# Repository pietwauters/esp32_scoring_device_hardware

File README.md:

# esp32_scoring_device_hardware
Hardware files for the [low cost scoring device based on a esp32 development board](https://github.com/pietwauters/esp32-scoring-device/wiki). The Wiki is slightly outdated as we now use an update for the PCB. It is just there for historical reasons. There is a [walkthrough on how to assemble the scoring device](https://github.com/pietwauters/esp32_scoring_device_hardware/blob/main/Walkthrough%20to%20buildOpenPiste%20%20Fencing%20Scoring%20Machine.docx).
The current firmware is found on [latest version of the firmware](https://github.com/pietwauters/esp32scoringdeviceMqtt)

You can use the same hardware to make an accurate [wire / weapon tester](https://github.com/pietwauters/WeaponWireTester). (You only have to replace the 470 Ohm resitors by 47 Ohm resistor) See: https://github.com/pietwauters/WeaponWireTester

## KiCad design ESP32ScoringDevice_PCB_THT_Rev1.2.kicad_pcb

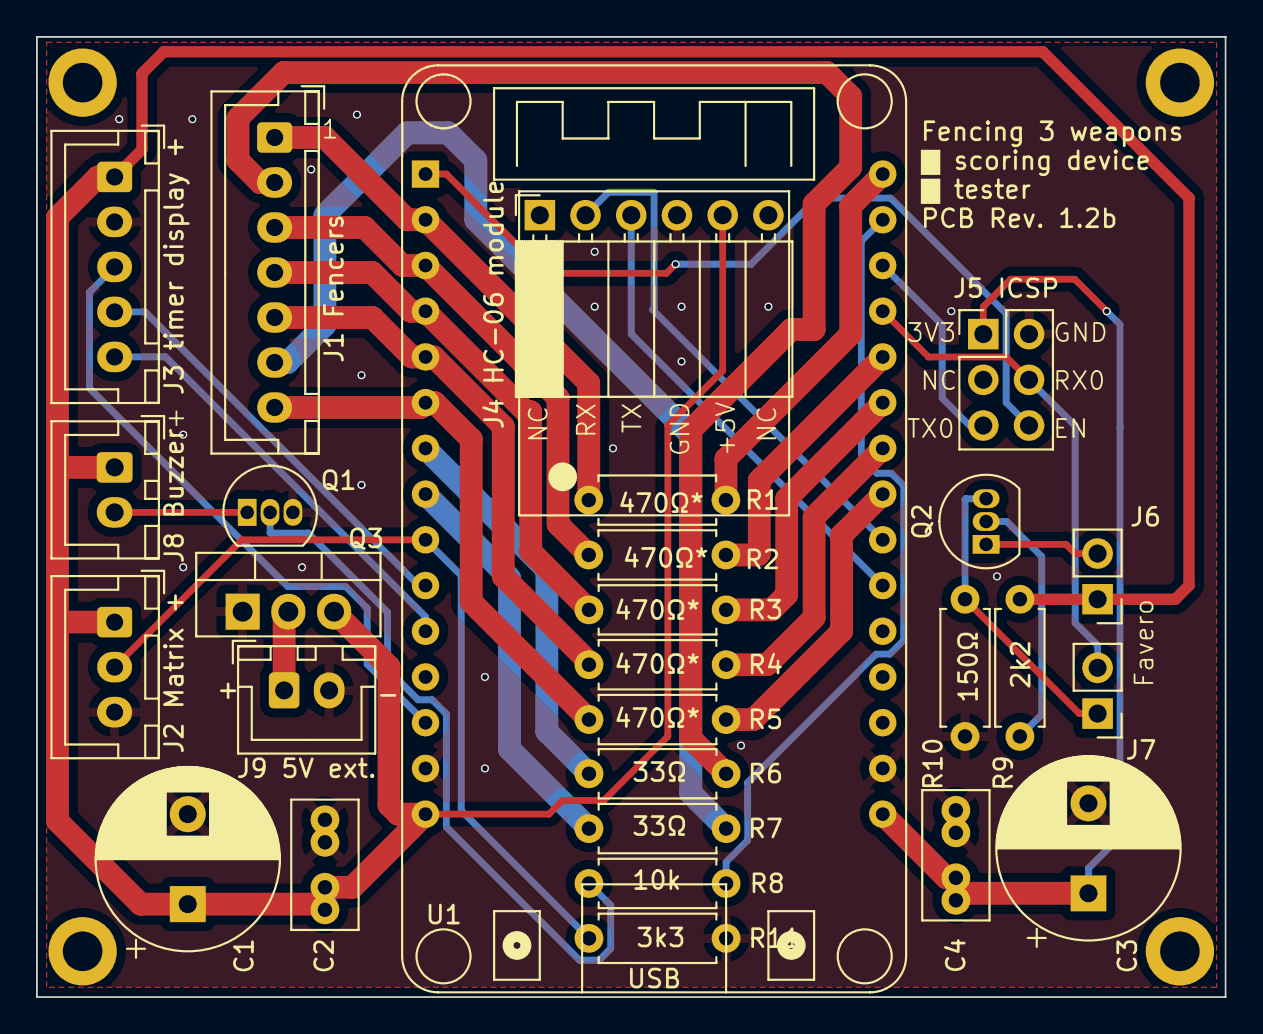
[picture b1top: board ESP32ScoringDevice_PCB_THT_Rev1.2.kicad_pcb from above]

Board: 2 copper layers, 66.0 x 53.3 mm, 32 parts (0 on the bottom side), 33 nets.

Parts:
C1, C3: 470µF; CP_Radial_D10.0mm_P5.00mm
C2, C4: 100nF; C_Rect_L7.0mm_W3.5mm_P2.50mm_P5.00mm
H1, H2, H3, H4: MountingHole_2.2mm_M2_DIN965_Pad
J1 Fencers: Fencers; JST_XH_B7B-XH-A_1x07_P2.50mm_Vertical
J2 Matrix +: WS2812B LED Matrix; JST_XH_B3B-XH-A_1x03_P2.50mm_Vertical
J3 timer display +: MAX7219 Timer Display; JST_XH_B5B-XH-A_1x05_P2.50mm_Vertical
J4 HC-06 module: HC-06 BT module; PinSocket_1x06_P2.54mm_Horizontal
J5 ICSP: ICSP; PinHeader_2x03_P2.54mm_Vertical
J6, J7: Conn_01x02; PinHeader_1x02_P2.54mm_Vertical
J8 Buzzer: Buzzer; JST_XH_B2B-XH-A_1x02_P2.50mm_Vertical
J9 5V ext.: 5V ext. Power; JST_XH_B2B-XH-A_1x02_P2.50mm_Vertical
Q1, Q2: BC337; TO-92_Inline
Q3: FQP27P06; TO-220-3_Vertical
R1, R2, R3, R4, R5: 470Ω; R_Axial_DIN0207_L6.3mm_D2.5mm_P7.62mm_Horizontal
R6, R7: 33Ω; R_Axial_DIN0207_L6.3mm_D2.5mm_P7.62mm_Horizontal
R8: 3k3; R_Axial_DIN0207_L6.3mm_D2.5mm_P7.62mm_Horizontal
R9: 2k2; R_Axial_DIN0207_L6.3mm_D2.5mm_P7.62mm_Horizontal
R10: 150Ω; R_Axial_DIN0207_L6.3mm_D2.5mm_P7.62mm_Horizontal
R11: 10k; R_Axial_DIN0207_L6.3mm_D2.5mm_P7.62mm_Horizontal
U1: ESP32_DevKit_V1_DOIT 30pin; esp32_devkit_v1_doit

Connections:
+3.3V: C3.1, C4.1, J5 ICSP.1, U1.16 (3V3)
+5V: C1.1, C2.1, J2 Matrix +.1, J3 timer display +.1, J4 HC-06 module.5, J6.1, J8 Buzzer.1, Q3.3 (S), R9.2, U1.15 (VIN)
GND: C1.2, C2.2, C3.2, C4.2, J2 Matrix +.3, J3 timer display +.2, J4 HC-06 module.4, J5 ICSP.2, J9 5V ext..2, Q1.3 (E), Q3.1 (G), R10.2, R11.2, U1.14 (GND), U1.17 (GND)
unnamed: J1 Fencers.1, R1.2, U1.2 (SENSOR_VP)
unnamed: J1 Fencers.2, R6.2
unnamed: J1 Fencers.3, R2.1, U1.3 (SENSOR_VN)
unnamed: J1 Fencers.4, R3.2, U1.4 (IO34)
unnamed: J1 Fencers.5, R4.2, U1.5 (IO35)
unnamed: J1 Fencers.6, R7.2
unnamed: J1 Fencers.7, R5.2, U1.6 (IO32)
unnamed: J2 Matrix +.2, R11.1, U1.9 (IO26)
unnamed: J3 timer display +.3, U1.13 (IO13)
unnamed: J3 timer display +.4, U1.10 (IO27)
unnamed: J3 timer display +.5, U1.11 (IO14)
unnamed: J4 HC-06 module.2, U1.22 (IO17)
unnamed: J4 HC-06 module.3, U1.21 (IO16)
unnamed: J5 ICSP.4, J7.2, U1.27 (RXD0/IO3)
unnamed: J5 ICSP.5, U1.28 (TXD0/IO1)
unnamed: J5 ICSP.6, U1.1 (EN)
unnamed: J6.2, Q2.1 (C)
unnamed: J7.1, Q2.3 (E), R10.1
unnamed: J8 Buzzer.2, Q1.1 (C)
unnamed: J9 5V ext..1, Q3.2 (D)
unnamed: Q1.2 (B), R8.1
unnamed: Q2.2 (B), R9.1
unnamed: R5.1, U1.23 (IO5)
unnamed: R4.1, U1.24 (IO18)
unnamed: R3.1, U1.25 (IO19)
unnamed: R2.2, U1.26 (IO21)
unnamed: R8.2, U1.29 (IO22)
unnamed: R1.1, U1.30 (IO23)
unnamed: R7.1, U1.8 (IO25)
unnamed: R6.1, U1.7 (IO33)

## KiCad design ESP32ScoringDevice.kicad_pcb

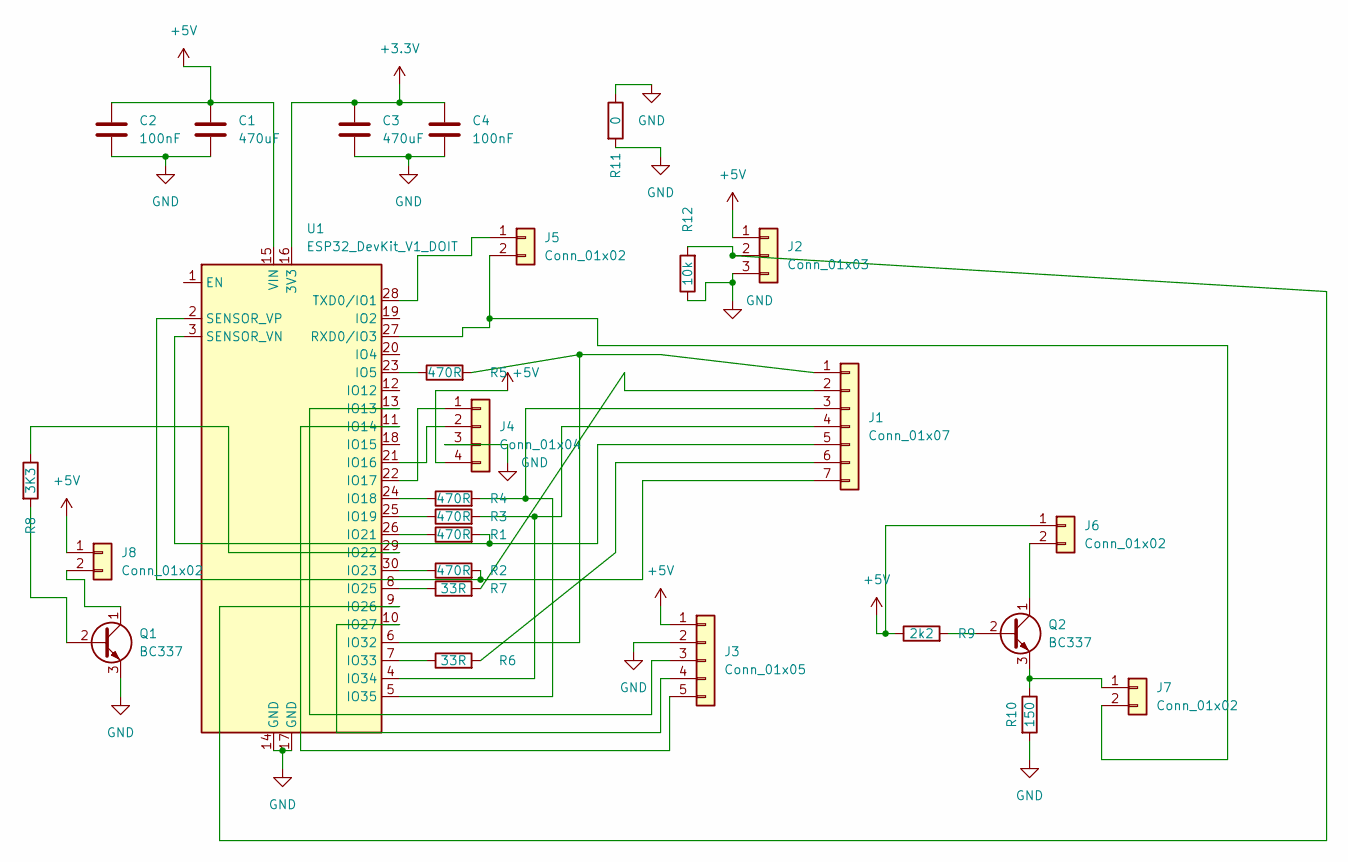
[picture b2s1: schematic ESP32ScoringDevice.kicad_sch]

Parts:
C1, C3: 470uF; CP_Radial_D10.0mm_P5.00mm
C2, C4: 100nF; C_Rect_L7.2mm_W2.5mm_P5.00mm_FKS2_FKP2_MKS2_MKP2
J1: Conn_01x07; PinHeader_1x07_P2.54mm_Vertical
J2: Conn_01x03; PinHeader_1x03_P2.54mm_Vertical
J3: Conn_01x05; PinHeader_1x05_P2.54mm_Vertical
J4: Conn_01x04; PinHeader_1x04_P2.54mm_Vertical
J5, J6, J7, J8: Conn_01x02; PinHeader_1x02_P2.54mm_Vertical
Q1, Q2: BC337; TO-92_Inline
R1, R2, R3, R4, R5: 470R; R_Axial_DIN0207_L6.3mm_D2.5mm_P10.16mm_Horizontal
R6, R7: 33R; R_Axial_DIN0207_L6.3mm_D2.5mm_P10.16mm_Horizontal
R8: 3K3; R_Axial_DIN0207_L6.3mm_D2.5mm_P10.16mm_Horizontal
R9: 2k2; R_Axial_DIN0207_L6.3mm_D2.5mm_P10.16mm_Horizontal
R10: 150; R_Axial_DIN0207_L6.3mm_D2.5mm_P10.16mm_Horizontal
R11: 0; R_Axial_DIN0207_L6.3mm_D2.5mm_P15.24mm_Horizontal
R12: 10k; R_Axial_DIN0207_L6.3mm_D2.5mm_P10.16mm_Horizontal
U1: ESP32_DevKit_V1_DOIT; esp32_devkit_v1_doit

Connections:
+3.3V: C3.1, C4.1, U1.16 (3V3)
+5V: C1.1, C2.1, J2.1, J3.1, J4.4, J6.1, J8.1, R9.1, U1.15 (VIN)
GND: C1.2, C2.2, C3.2, C4.2, J2.3, J3.2, J4.3, Q1.3 (E), R10.2, R11.1, R11.2, R12.1, U1.14 (GND), U1.17 (GND)
unnamed: J1.1, R5.2, U1.6 (IO32)
unnamed: J1.2, R7.2
unnamed: J1.3, R4.2, U1.5 (IO35)
unnamed: J1.4, R3.2, U1.4 (IO34)
unnamed: J1.5, R1.2, U1.3 (SENSOR_VN)
unnamed: J1.6, R6.2
unnamed: J1.7, R2.2, U1.2 (SENSOR_VP)
unnamed: J2.2, R12.2, U1.9 (IO26)
unnamed: J3.3, U1.13 (IO13)
unnamed: J3.4, U1.10 (IO27)
unnamed: J3.5, U1.11 (IO14)
unnamed: J4.1, U1.22 (IO17)
unnamed: J4.2, U1.21 (IO16)
unnamed: J5.1, U1.28 (TXD0/IO1)
unnamed: J5.2, J7.2, U1.27 (RXD0/IO3)
unnamed: J6.2, Q2.1 (C)
unnamed: J7.1, Q2.3 (E), R10.1
unnamed: J8.2, Q1.1 (C)
unnamed: Q1.2 (B), R8.2
unnamed: Q2.2 (B), R9.2
unnamed: R1.1, U1.26 (IO21)
unnamed: R2.1, U1.30 (IO23)
unnamed: R3.1, U1.25 (IO19)
unnamed: R4.1, U1.24 (IO18)
unnamed: R5.1, U1.23 (IO5)
unnamed: R6.1, U1.7 (IO33)
unnamed: R7.1, U1.8 (IO25)
unnamed: R8.1, U1.29 (IO22)

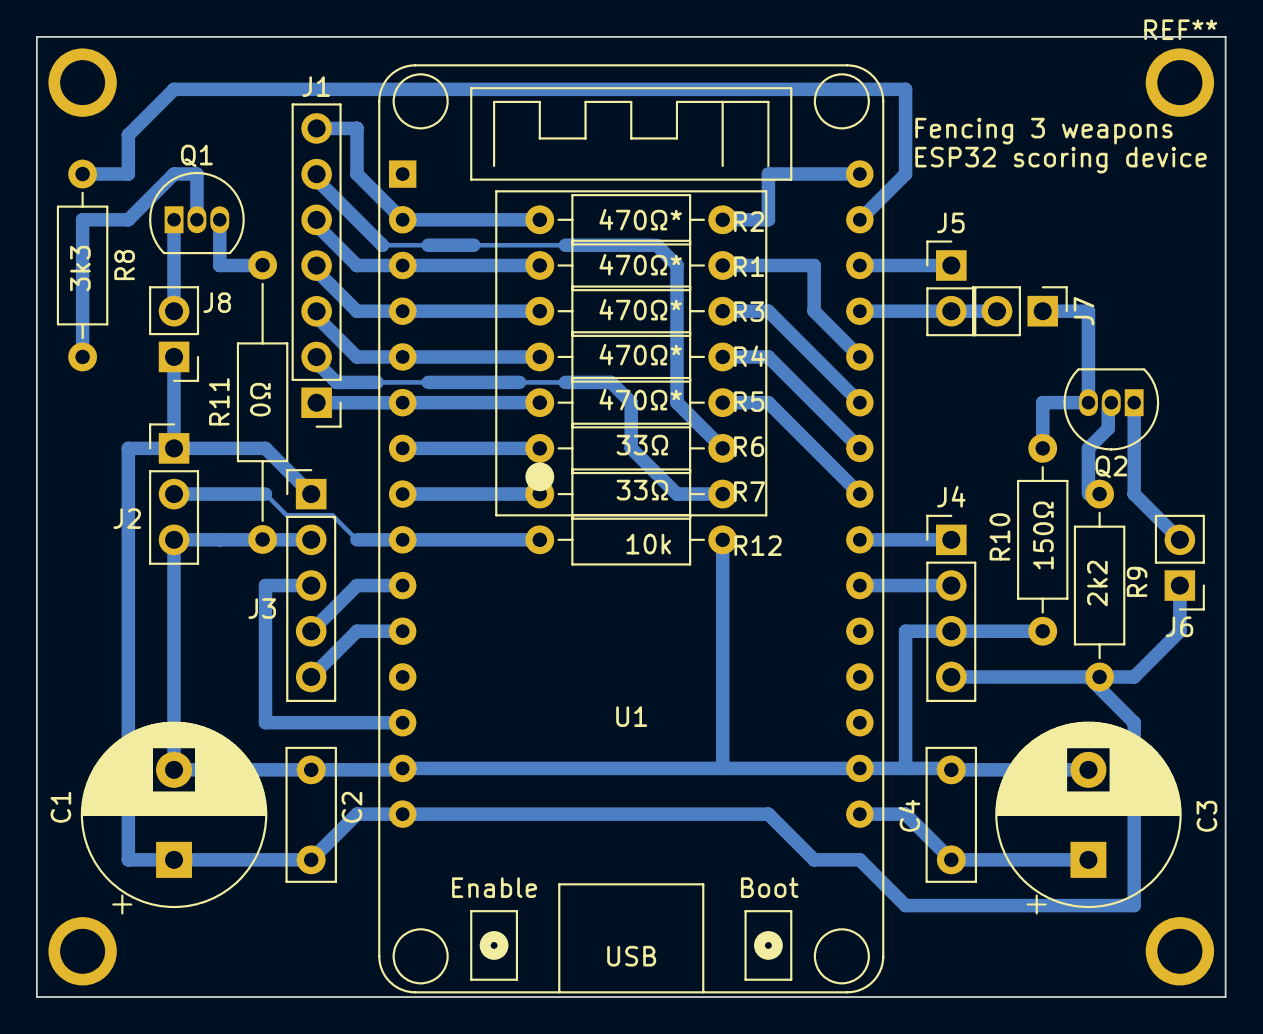
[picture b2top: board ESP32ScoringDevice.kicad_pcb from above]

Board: 2 copper layers, 66.0 x 53.3 mm, 27 parts (0 on the bottom side), 31 nets.

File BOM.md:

# BOM - Bill of materials  

> [!NOTE]
> All items marked with * are optional. JST or header connectors can be substituted by soldering the wires directly to the board or ESP.

> [!TIP]
> JST- XH 2.54mm are the recommended connector type for J1-J8 because they are keyed and you can't connect them the wrong way.
> Simple header pins work fine too, but make sure to orient the plug correctly. 
> JSTs can be bought as kit with wire and crimper. 
> Connectors are preferred over soldering directly because of serviceability.

## 3 weapon scoring device

| N° of pieces | Designator | Description | Value | Size | Remarks |
| --- | --- | --- | --- | --- | --- |
| 1* | | PCB |Rev 1.0|| alternatively you could build the circuit on a breadboard or perfboard|
| 1 | U1 | ESP32 DevKit V1 |  |  |  be sure to get the **30 pin** version (2 x 15). There are many board flavors out there e.g. V4 is 38 pin |
| 2 |  | 64 LED matrix panel | WS2812B-64 led matrix | 65mm x 65mm | |
| 1* |  | MAX7219 Dot matrix Module 4-in-1 LED Display module | | | |
| 2 | C1,C3 | radial electrolytic capacitor | 470µF - 35V | Ø10mm - 5mm pitch |   |
| 2 | C2,C4 | polyester film capacitor | 0,1µF | L7,3 x W2,5mm | |
| 2 | Q1,Q2 | BC337 NPN transistor | 0,8A 45V | TO92 | | |
| 5 | R1,R2,R3,R4,R5 | metal film resistor | 470Ω 1% | 1/4W | |
| 2 | R6,R7 | metal film resistor | 33Ω 1% | 1/4W | |
| 1 | R8 | metal film resistor | 3,3kΩ 1% | 1/4W | |
| 1 | R9 | metal film resistor | 2,2kΩ 1% | 1/4W | |
| 1 | R10 | metal film resistor | 150Ω 1% | 1/4W | |
| 1* | R11 | metal film resistor | 0Ω bridge | 1/4W | can be substituted by a simple wire bridge |
| 7 |  | female banana jack | | 4mm, panel mount | |
| 1 | R12 | metal film resistor | 10kΩ 1% | 1/4W | |
| 1* | J1 | JST connector | 1 x 7 | 2,54mm pitch | |
| 1* | J2 | JST connector | 1 x 3 | 2,54mm pitch | |
| 1* | J3 | JST connector | 1 x 5 | 2,54mm pitch | |
| 1* | J4 | JST connector | 1 x 4 | 2,54mm pitch | |
| 4* | J5,J6,J7,J8 | JST connector | 1 x 2 | 2,54mm pitch | |
| 2* |  | pin strip, socket (female) | 1 x 15 | 2,54mm pitch | header for the ESP32 board |


## Weapons / body wire tester

| N° of pieces | Designator | Description | Value | Size | Remarks |
| --- | --- | --- | --- | --- | --- |
| 1* | | PCB |Rev 1.0|| alternatively you could build the circuit on a breadboard or perfboard|
| 1 | U1 | ESP32 DevKit V1 |   |   |  be sure to get the **30 pin** version (2 x 15). There are many board flavors out there e.g. V4 is 38 pin |
| 1 |  | 25 LED matrix panel | WS2812B-25 led matrix | 38mm x 38mm | |
| 2 | C1,C3 | radial electrolytic capacitor | 470µF - 35V | Ø10mm - 5mm pitch |   |
| 2 | C2,C4 | polyester film capacitor | 0,1µF | L7,3 x W2,5mm | |
| 5 | R1,R2,R3,R4,R5 | metal film resistor | **47Ω 1%** | 1/4W | These resistors are marked 470Ω* on the silkscreen |
| 2 | R6,R7 | metal film resistor | 33Ω 1% | 1/4W | |
| 1* | R11 | metal film resistor | 0Ω bridge | 1/4W | can be substituted by a simple wire bridge |
| 7 |  | female banana jack | | 4mm, panel mount | |
| 1* | J1 | JST connector | 1 x 7 | 2,54mm pitch | |
| 1* | J2 | JST connector | 1 x 3 | 2,54mm pitch | |

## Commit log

2022-09-22 inititial commit
2023-01-22 Added 10k pull down resistor on the data line of the SW2812b matrices
2024-12-29 Rev 1.1 of the PCB
    Changelog:
    - created ground planes on both sides. R11 is obsolete. Tests have to show if they interfere with Wifi signal. If so, the antenna area has to be spared out more consequently.
    - rerouted the board on 2 sides. No difference in cost if 1 or 2 sided PCB.
    - increased the trace width to 50mil (1,27mm) for less resistance and more consistent resistance values between traces.
    - test boards are ordered, real world tests have to show if this revision is viable. No commit to main branch before validation!
2025-01-20 Board Rev. 1.2
2025-01-26 new board rev. 1.2
2025-02-15 Rev 1.2b
    Small tweaks
2025-02-15 Rev1.2b
2025-04-02 build images for wiki
2026-06-08 Enhance README with additional project details
    Updated README to include information about PCB updates, assembly walkthrough, and current firmware location.

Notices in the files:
ESP32ScoringDevice.kicad_pcb:
©Piet Wauters 2024 GNU GPL V3.0
